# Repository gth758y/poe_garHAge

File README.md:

# poe_garHAge

in-work version of the PoE powered, MQTT garage door controller

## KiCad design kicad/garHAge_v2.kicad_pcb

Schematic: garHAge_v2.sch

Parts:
C1, C2: 6.8n; C_0805_2012Metric
C3: 22n; C_0805_2012Metric
C4: 10n; C_0805_2012Metric
C5, C6: 18p; C_0603_1608Metric
C7, C8, C9: 100n; C_0805_2012Metric
D1: BLUE; LED_1206_3216Metric_Pad1.42x1.75mm_HandSolder
D2: RED; LED_1206_3216Metric_Pad1.42x1.75mm_HandSolder
J1, J2, J3: SJ1-2503A; Headphone_Jack_2.5mm_SJ1-2503A; MPN SJ1-2503A; Digi-Key_PN CP1-2503A-ND
J4: 0813-1X1T-57-F; 0813-1X1T-57-F_RJ45-Jack; DigiKey Part Number 507-1421-ND
L1: 1uH; C_0805_2012Metric
R1, R2, R3, R4: 49.9; R_0805_2012Metric
R5, R7: 330; R_0805_2012Metric
R6: 12k; R_0805_2012Metric
U1: ATMEGA328P-AU; TQFP-32_7x7mm; MPN ATMEGA328P-AU; Digi-Key_PN ATMEGA328P-AU-ND
X1: ICSP; PinHeader_2x03_P2.54mm_Vertical
X2: Serial Pwr Disconnect; PinHeader_1x02_P2.54mm_Vertical
X3: Serial Interface; PinHeader_1x06_P2.54mm_Horizontal
Y1: 8MHz; Crystal_SMD_5032-2Pin_5.0x3.2mm

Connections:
+3V3: C8.1, C9.1, L1.1, R1.1, R2.1, R5.2, R6.2, U1.4 (VCC), U1.6 (VCC), U1.18 (AVCC), U1.20 (AREF), X1.2, X2.2; also elsewhere on the board
/BOOT_STATUS: D2.2 (A), R7.2
/CT: C3.2, J4.7 (CT), L1.2
/PoE_PD_Interface/VC12: J4.5 (VC12); also elsewhere on the board
/PoE_PD_Interface/VC36: J4.10 (VC36); also elsewhere on the board
/PoE_PD_Interface/VC45: J4.6 (VC45); also elsewhere on the board
/PoE_PD_Interface/VC78: J4.11 (VC78); also elsewhere on the board
/RD+: C2.2, J4.2 (RD+), R3.2
/RD-: C1.2, J4.9 (RD-), R4.2
/W5100_Ethernet_Interface/RD+: C2.1; also elsewhere on the board
/W5100_Ethernet_Interface/RD-: C1.1; also elsewhere on the board
/W5100_Ethernet_Interface/TD+: J4.1 (TD+), R1.2; also elsewhere on the board
/W5100_Ethernet_Interface/TD-: J4.8 (TD-), R2.2; also elsewhere on the board
D1RELAY: U1.9 (PD5); also elsewhere on the board
D1SENSOR: J1.1 (S), U1.10 (PD6)
D2RELAY: U1.2 (PD4); also elsewhere on the board
D2SENSOR: J2.1 (S), U1.11 (PD7)
D3RELAY: U1.1 (PD3); also elsewhere on the board
D3SENSOR: J3.1 (S), U1.12 (PB0)
DTR: C7.1, X3.6
GND: C3.1, C4.1, C5.1, C6.2, C8.2, C9.2, D1.1 (K), D2.1 (K), J1.4 (R), J2.4 (R), J3.4 (R), U1.3 (GND), U1.5 (GND), U1.21 (GND), X1.6, X3.1, X3.2; also elsewhere on the board
INT: U1.32 (PD2); also elsewhere on the board
MISO: U1.16 (PB4), X1.1; also elsewhere on the board
MOSI: U1.15 (PB3), X1.4; also elsewhere on the board
unnamed: C4.2, R3.1, R4.1
unnamed: C5.2, U1.7 (PB6), Y1.1
unnamed: C6.1, U1.8 (PB7), Y1.2
unnamed: D1.2 (A), R5.1
unnamed: R7.1, U1.25 (PC2)
unnamed: X2.1, X3.3
RESET: C7.2, R6.1, U1.29 (PC6), X1.5; also elsewhere on the board
RXI: U1.30 (PD0), X3.4
SCK: U1.17 (PB5), X1.3; also elsewhere on the board
SS: U1.14 (PB2); also elsewhere on the board
TXO: U1.31 (PD1), X3.5

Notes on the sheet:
ICSP Interface
Serial Debug Interface
Power Indication
Relay Interface
Reed Switch Interface
Ethernet and 802.3af PoE Interface
ATMEGA328P MCU

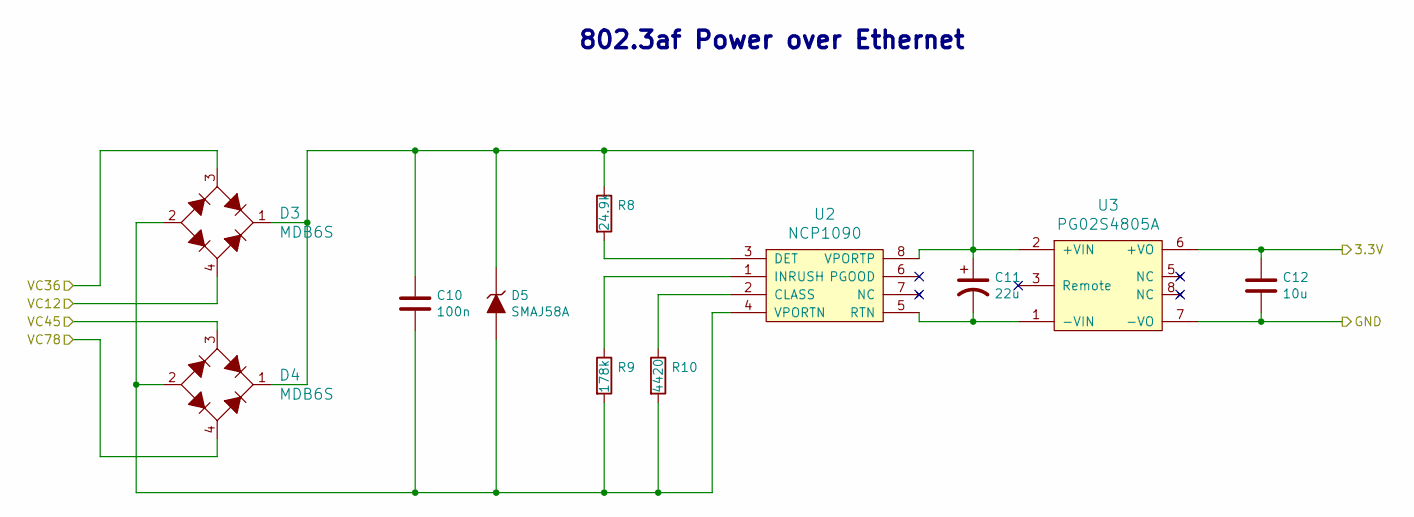
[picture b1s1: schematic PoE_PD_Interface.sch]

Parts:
C10: 100n; C_0805_2012Metric
C11: 22u; CP_Radial_D5.0mm_P2.00mm
C12: 10u; C_0805_2012Metric
D3, D4: MDB6S; Micro-DIP-4; DigiKey Part Number MDB6SFSCT-ND
D5: SMAJ58A; D_SMA
R8: 24.9k; R_0805_2012Metric
R9: 178k; R_0805_2012Metric
R10: 4420; R_0805_2012Metric
U2: NCP1090; SOIC-8_3.9x4.9mm_P1.27mm; DigiKey Part Number NCP1090DGOS-ND
U3: PG02S4805A; PG02S; DigiKey Part Number 941-1186-ND

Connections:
+3V3: C12.1, U3.6 (+VO); also elsewhere on the board
/PoE_PD_Interface/VC12: D3.4 (AC2); also elsewhere on the board
/PoE_PD_Interface/VC36: D3.3 (AC1); also elsewhere on the board
/PoE_PD_Interface/VC45: D4.3 (AC1); also elsewhere on the board
/PoE_PD_Interface/VC78: D4.4 (AC2); also elsewhere on the board
GND: C12.2, U3.7 (-VO); also elsewhere on the board
unnamed: C10.1, C11.1, D3.1 (+), D4.1 (+), D5.1 (K), R8.1, U2.8 (VPORTP), U3.2 (+VIN)
unnamed: C10.2, D3.2 (-), D4.2 (-), D5.2 (A), R9.2, R10.2, U2.4 (VPORTN)
unnamed: C11.2, U2.5 (RTN), U3.1 (-VIN)
unnamed: R8.2, U2.3 (DET)
unnamed: R9.1, U2.1 (INRUSH)
unnamed: R10.1, U2.2 (CLASS)

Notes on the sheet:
802.3af Power over Ethernet

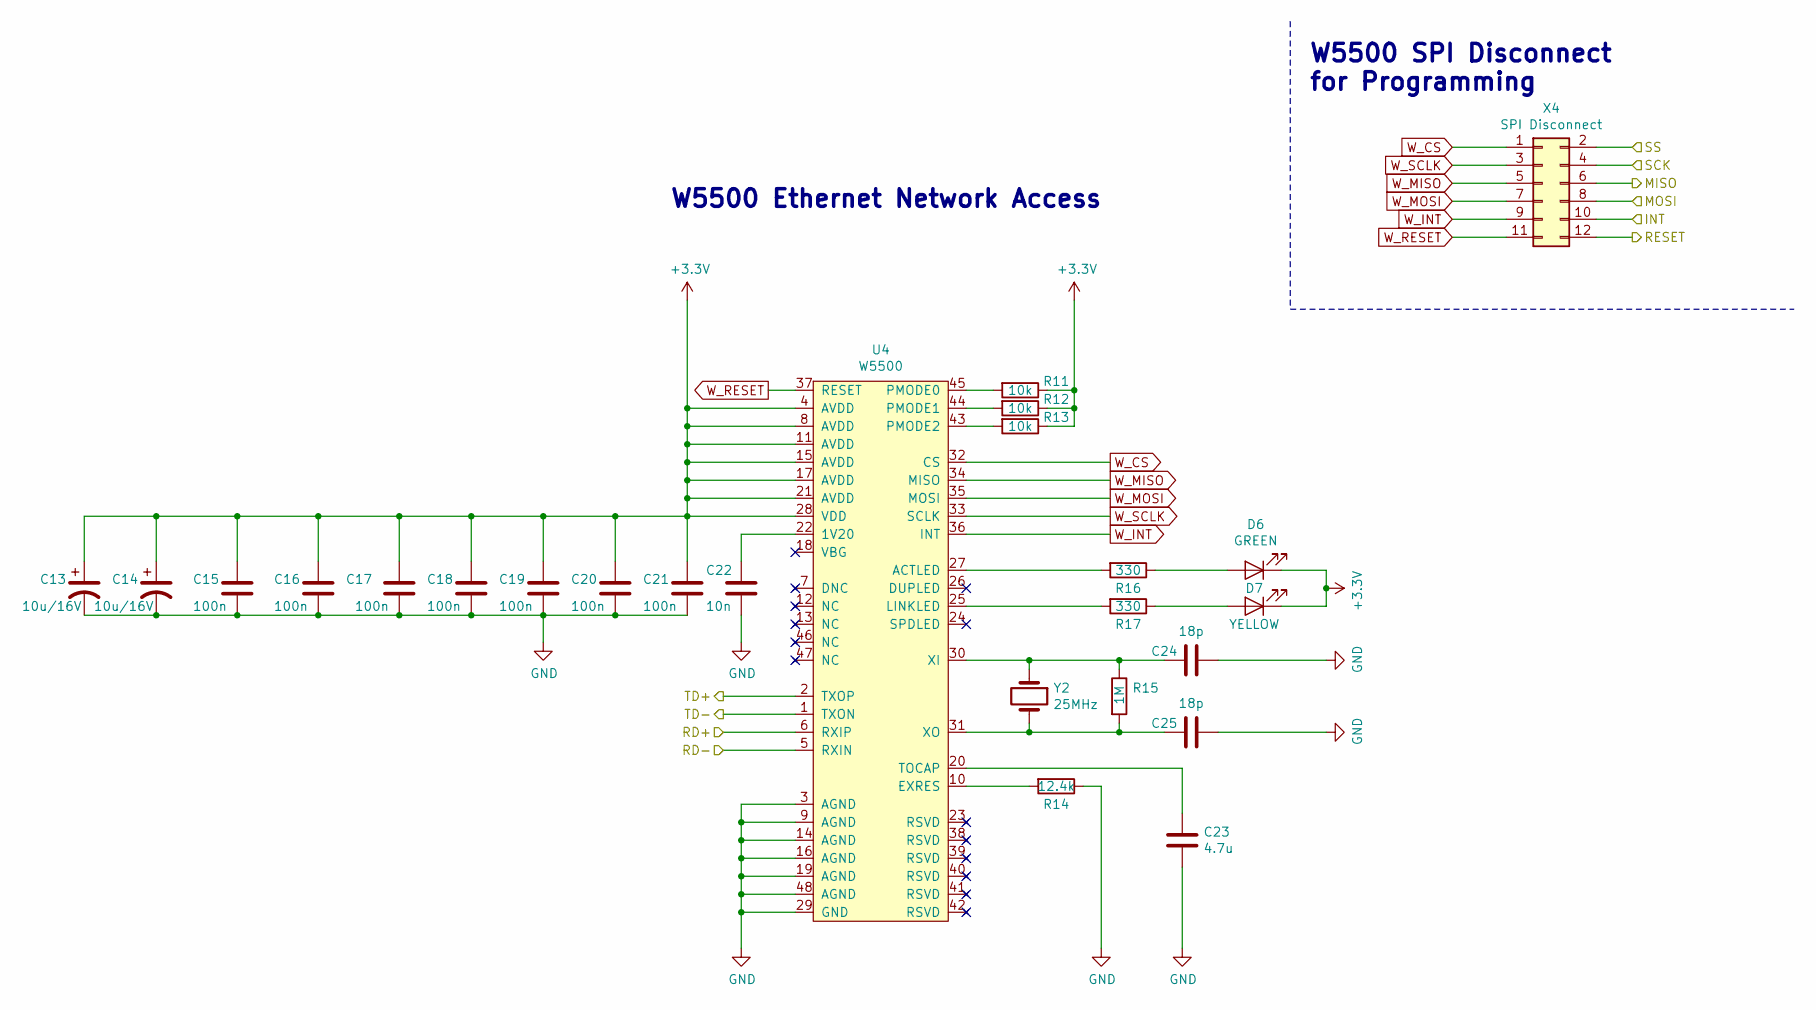
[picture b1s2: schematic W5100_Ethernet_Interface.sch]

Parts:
C13, C14: 10u/16V; C_0805_2012Metric
C15, C16, C17, C18, C19, C20, C21: 100n; C_0805_2012Metric
C22: 10n; C_0805_2012Metric
C23: 4.7u; C_0805_2012Metric
C24, C25: 18p; C_0603_1608Metric
D6: GREEN; LED_1206_3216Metric_Pad1.42x1.75mm_HandSolder
D7: YELLOW; LED_1206_3216Metric_Pad1.42x1.75mm_HandSolder
R11, R12, R13: 10k; R_0805_2012Metric
R14: 12.4k; R_0805_2012Metric
R15: 1M; R_0805_2012Metric
R16, R17: 330; R_0805_2012Metric
U4: W5500; LQFP-48_7x7mm_P0.5mm
X4: SPI Disconnect; PinHeader_2x06_P2.54mm_Vertical
Y2: 25MHz; Crystal_SMD_5032-2Pin_5.0x3.2mm

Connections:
+3V3: C13.1, C14.1, C15.1, C16.1, C17.1, C18.1, C19.1, C20.1, C21.1, D6.1 (K), D7.1 (K), R11.1, R12.1, R13.1, U4.4 (AVDD), U4.8 (AVDD), U4.11 (AVDD), U4.15 (AVDD), U4.17 (AVDD), U4.21 (AVDD), U4.28 (VDD); also elsewhere on the board
/W5100_Ethernet_Interface/RD+: U4.6 (RXIP); also elsewhere on the board
/W5100_Ethernet_Interface/RD-: U4.5 (RXIN); also elsewhere on the board
/W5100_Ethernet_Interface/TD+: U4.2 (TXOP); also elsewhere on the board
/W5100_Ethernet_Interface/TD-: U4.1 (TXON); also elsewhere on the board
GND: C13.2, C14.2, C15.2, C16.2, C17.2, C18.2, C19.2, C20.2, C21.2, C22.2, C23.2, C24.1, C25.1, R14.1, U4.3 (AGND), U4.9 (AGND), U4.14 (AGND), U4.16 (AGND), U4.19 (AGND), U4.29 (GND), U4.48 (AGND); also elsewhere on the board
INT: X4.10; also elsewhere on the board
MISO: X4.6; also elsewhere on the board
MOSI: X4.8; also elsewhere on the board
unnamed: C22.1, U4.22 (1V20)
unnamed: C23.1, U4.20 (TOCAP)
unnamed: C24.2, R15.1, U4.30 (XI), Y2.1
unnamed: C25.2, R15.2, U4.31 (XO), Y2.2
unnamed: D6.2 (A), R16.1
unnamed: D7.2 (A), R17.1
unnamed: R11.2, U4.45 (PMODE0)
unnamed: R12.2, U4.44 (PMODE1)
unnamed: R13.2, U4.43 (PMODE2)
unnamed: R14.2, U4.10 (EXRES)
unnamed: R16.2, U4.27 (ACTLED)
unnamed: R17.2, U4.25 (LINKLED)
RESET: X4.12; also elsewhere on the board
SCK: X4.4; also elsewhere on the board
SS: X4.2; also elsewhere on the board
W_CS: U4.32 (CS), X4.1
W_INT: U4.36 (INT), X4.9
W_MISO: U4.34 (MISO), X4.5
W_MOSI: U4.35 (MOSI), X4.7
W_RESET: U4.37 (RESET), X4.11
W_SCLK: U4.33 (SCLK), X4.3

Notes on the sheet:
W5500 SPI Disconnect for Programming
W5500 Ethernet Network Access

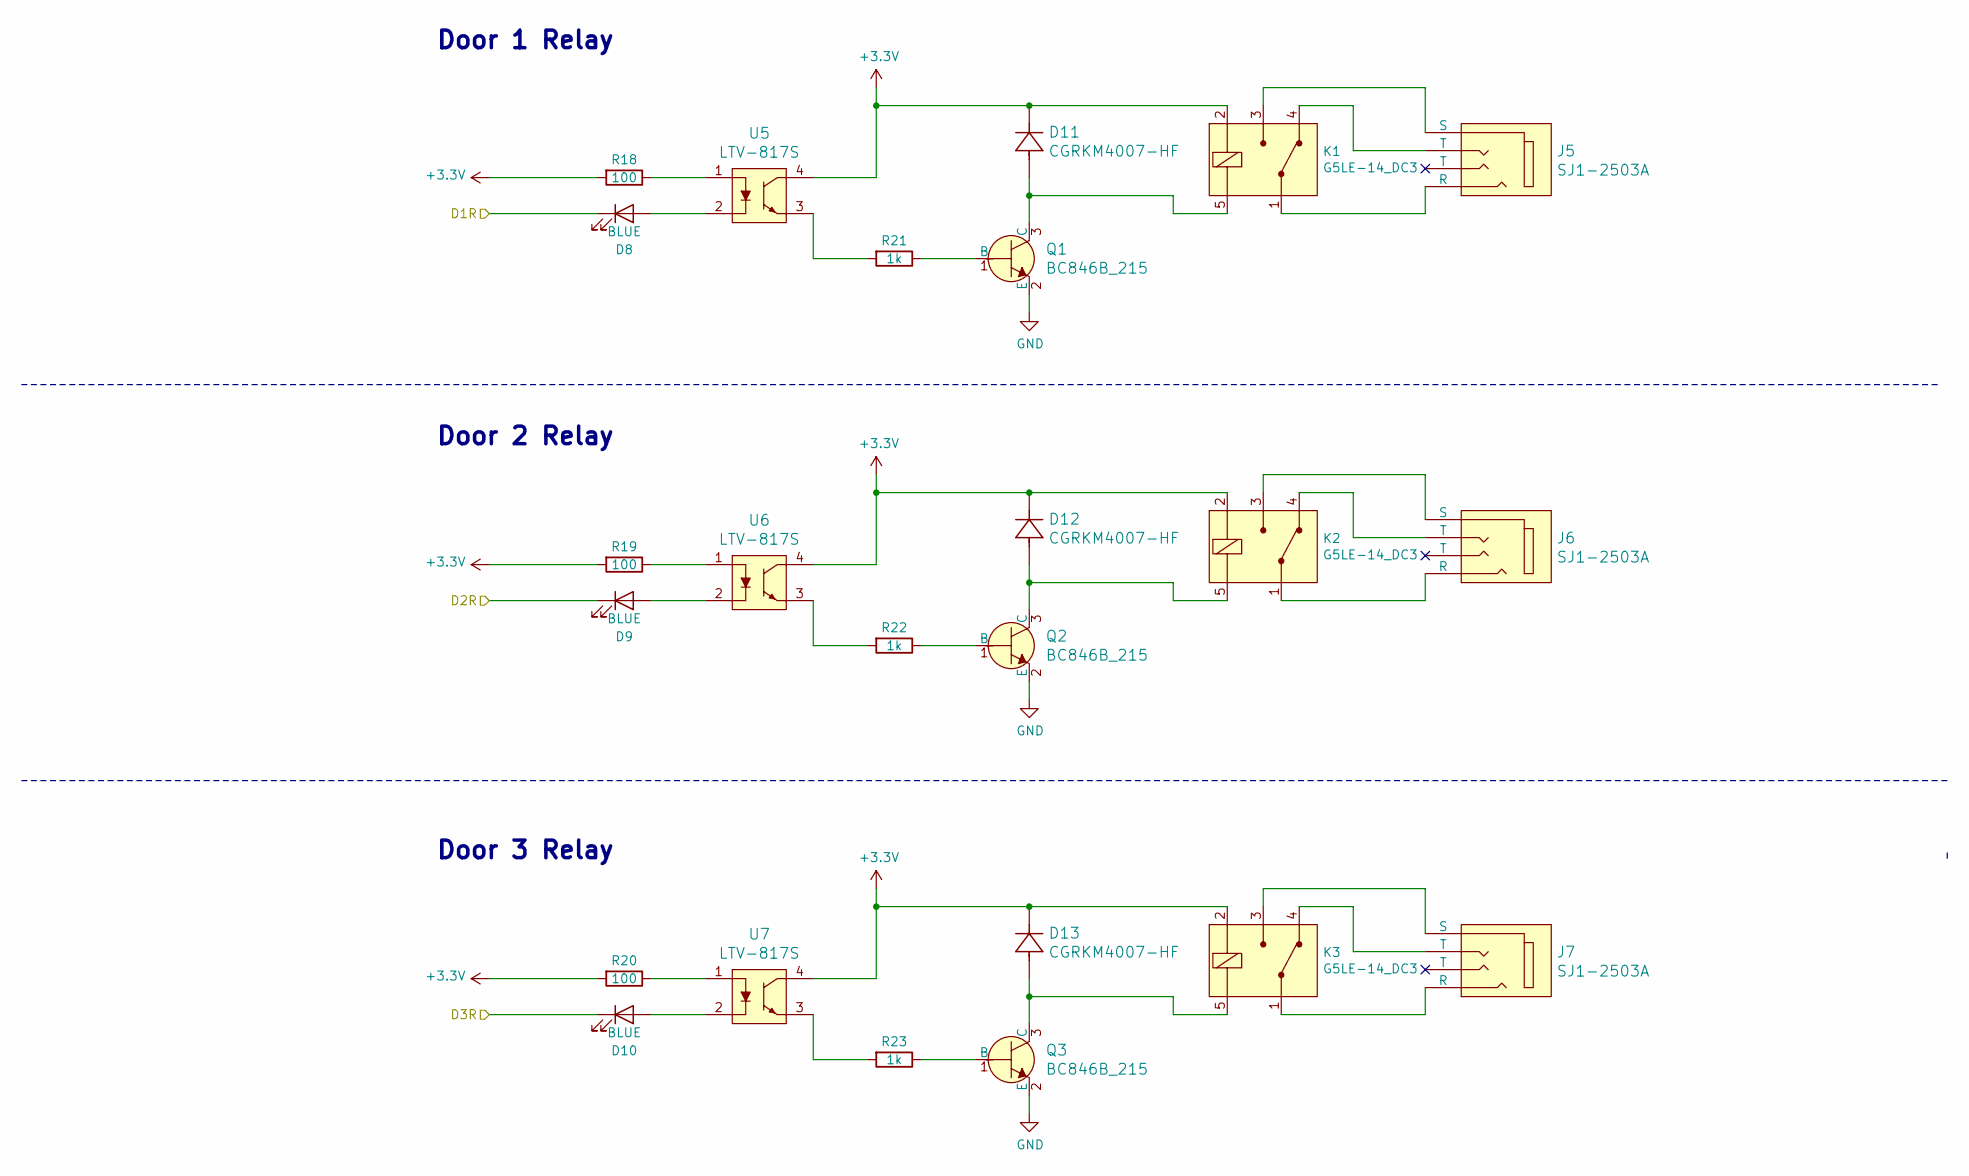
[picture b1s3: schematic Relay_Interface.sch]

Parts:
D8, D9, D10: BLUE; LED_1206_3216Metric_Pad1.42x1.75mm_HandSolder
D11, D12, D13: CGRKM4007-HF; D_SOD-123F
J5, J6, J7: SJ1-2503A; Headphone_Jack_2.5mm_SJ1-2503A; MPN SJ1-2503A; Digi-Key_PN CP1-2503A-ND
K1, K2, K3: G5LE-14_DC3; Relay_THT_G5LE-14; MPN G5LE-14 DC3; Digi-Key_PN Z3326-ND
Q1, Q2, Q3: BC846B_215; SOT-23-3; MPN BC846B,215; Digi-Key_PN 1727-2920-1-ND
R18, R19, R20: 100; R_0805_2012Metric
R21, R22, R23: 1k; R_0805_2012Metric
U5: LTV-817S; DIP-4_SMD_GullWing; MPN LTV-817; Digi-Key_PN 160-1366-5-ND
U6, U7: LTV-817S; DIP-4_SMD_GullWing; MPN LTV-817S; Digi-Key_PN 160-1366-5-ND

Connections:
+3V3: D11.1, D12.1, D13.1, K1.2 (COIL), K2.2 (COIL), K3.2 (COIL), R18.2, R19.2, R20.2, U5.4, U6.4, U7.4; also elsewhere on the board
D1RELAY: D8.1 (K); also elsewhere on the board
D2RELAY: D9.1 (K); also elsewhere on the board
D3RELAY: D10.1 (K); also elsewhere on the board
GND: Q1.2 (E), Q2.2 (E), Q3.2 (E); also elsewhere on the board
unnamed: D8.2 (A), U5.2
unnamed: D9.2 (A), U6.2
unnamed: D10.2 (A), U7.2
unnamed: D11.2, K1.5 (COIL), Q1.3 (C)
unnamed: D12.2, K2.5 (COIL), Q2.3 (C)
unnamed: D13.2, K3.5 (COIL), Q3.3 (C)
unnamed: J5.1 (S), K1.3 (NO)
unnamed: J5.3 (T), K1.4 (NC)
unnamed: J5.4 (R), K1.1 (COM)
unnamed: J6.1 (S), K2.3 (NO)
unnamed: J6.3 (T), K2.4 (NC)
unnamed: J6.4 (R), K2.1 (COM)
unnamed: J7.1 (S), K3.3 (NO)
unnamed: J7.3 (T), K3.4 (NC)
unnamed: J7.4 (R), K3.1 (COM)
unnamed: Q1.1 (B), R21.1
unnamed: Q2.1 (B), R22.1
unnamed: Q3.1 (B), R23.1
unnamed: R18.1, U5.1
unnamed: R19.1, U6.1
unnamed: R20.1, U7.1
unnamed: R21.2, U5.3
unnamed: R22.2, U6.3
unnamed: R23.2, U7.3

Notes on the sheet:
Door 1 Relay
Door 2 Relay
Door 3 Relay

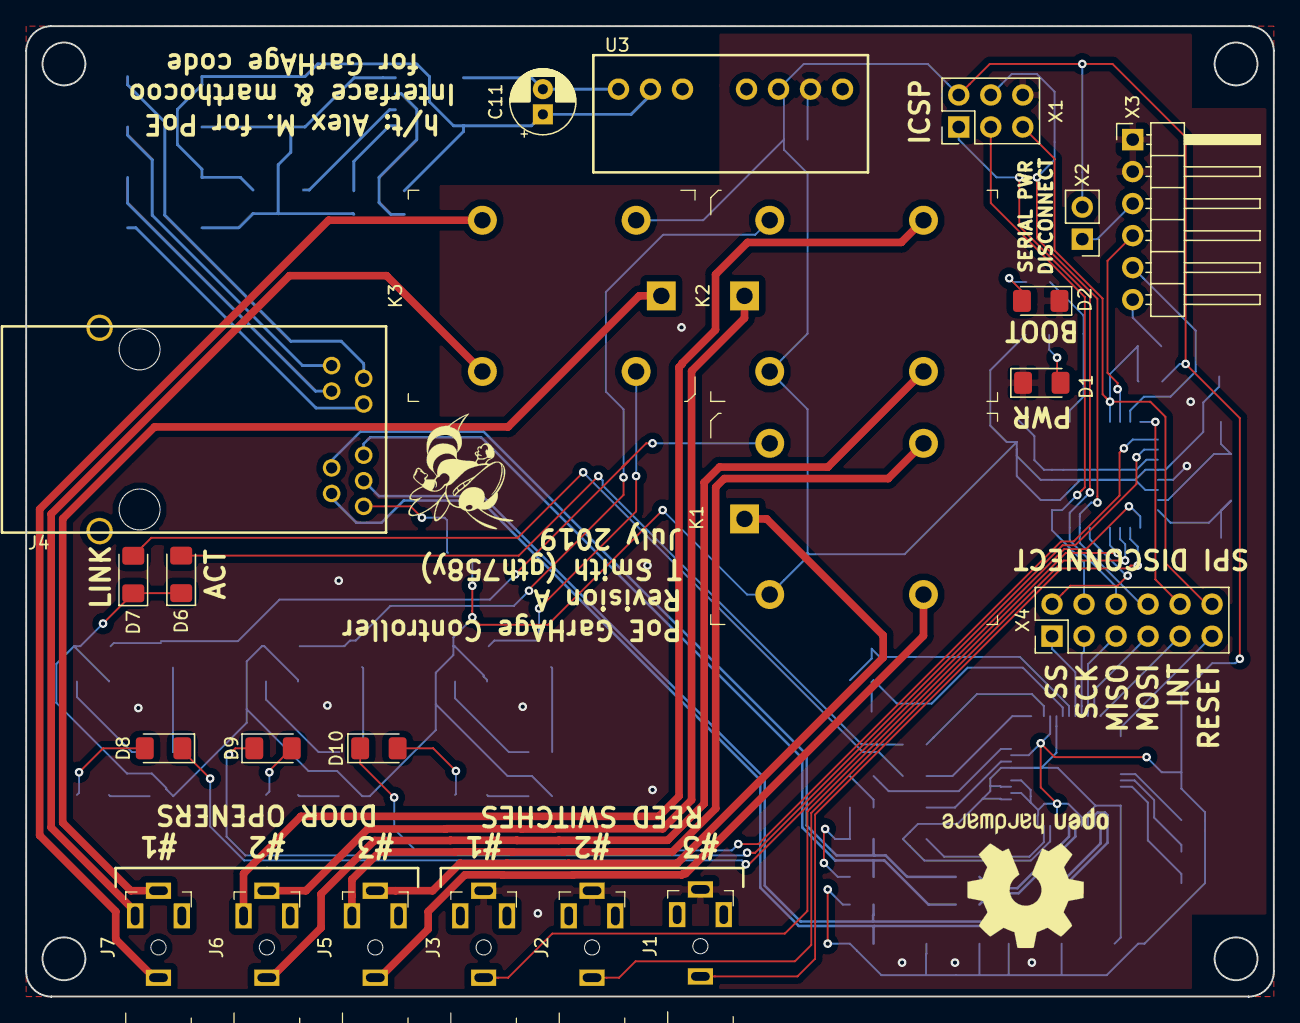
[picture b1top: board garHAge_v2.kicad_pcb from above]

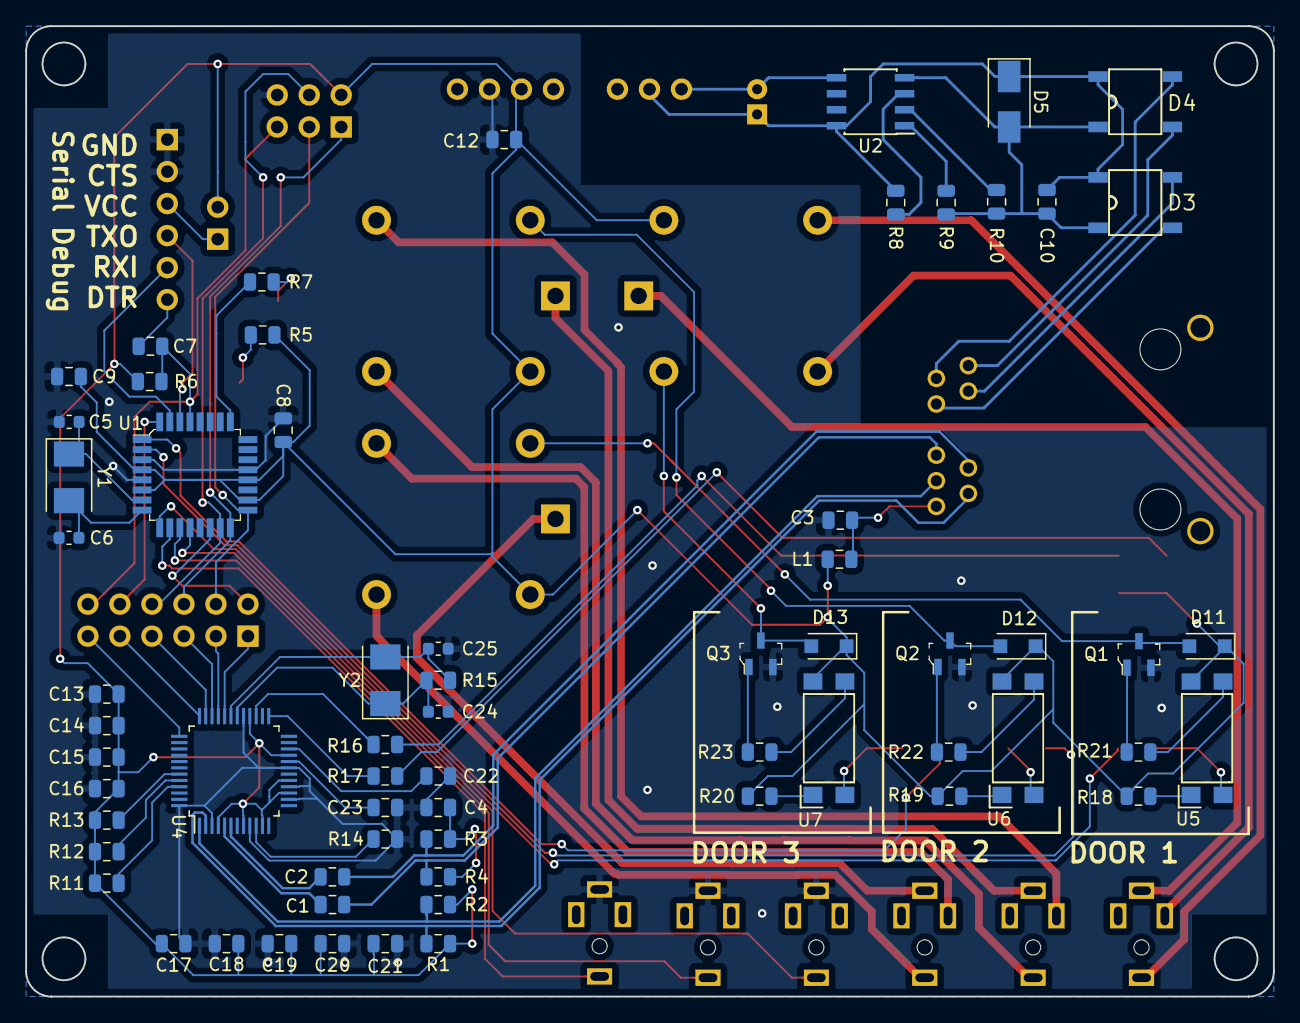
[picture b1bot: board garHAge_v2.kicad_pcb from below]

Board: 2 copper layers, 99.0 x 77.0 mm, 88 parts (65 on the bottom side), 83 nets.

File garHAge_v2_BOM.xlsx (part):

Source: | Z:\00 - tyler\arduino projects\poe garHAge\garHAge_v2\garHAge_v2.sch
Date: | 43660.793032407404
Tool: | Eeschema (5.0.2)-1
Generator: | C:\Program Files\KiCad\bin\scripting\plugins/bom_csv_grouped_by_value.py
Component Count: | 88
Individual Components:
Item | Qty | Reference(s) | Value | LibPart | Footprint | Digi-Key_PN | DigiKey Part Number | Description | Datasheet | Category | DK_Datasheet_Link | DK_Detail_Page | Family | MPN | Manufacturer | Status
 |  | C1 | 6.8n | Device:C | Capacitor_SMD:C_0805_2012Metric |  |  |  | ~
 |  | C2 | 6.8n | Device:C | Capacitor_SMD:C_0805_2012Metric |  |  |  | ~
 |  | C3 | 22n | Device:C | Capacitor_SMD:C_0805_2012Metric |  |  |  | ~
 |  | C4 | 10n | Device:C | Capacitor_SMD:C_0805_2012Metric |  |  |  | ~
 |  | C5 | 18p | Device:C | Capacitor_SMD:C_0603_1608Metric |  |  |  | ~
 |  | C6 | 18p | Device:C | Capacitor_SMD:C_0603_1608Metric |  |  |  | ~
 |  | C7 | 100n | Device:C | Capacitor_SMD:C_0805_2012Metric |  |  |  | ~
 |  | C8 | 100n | Device:C | Capacitor_SMD:C_0805_2012Metric |  |  |  | ~
 |  | C9 | 100n | Device:C | Capacitor_SMD:C_0805_2012Metric |  |  |  | ~
 |  | C10 | 100n | Device:C | Capacitor_SMD:C_0805_2012Metric |  |  |  | ~
 |  | C11 | 22u | Device:CP1 | Capacitor_THT:CP_Radial_D5.0mm_P2.00mm |  |  |  | ~
 |  | C12 | 10u | Device:C | Capacitor_SMD:C_0805_2012Metric |  |  |  | ~
 |  | C13 | 10u/16V | Device:CP1 | Capacitor_SMD:C_0805_2012Metric |  |  |  | ~
 |  | C14 | 10u/16V | Device:CP1 | Capacitor_SMD:C_0805_2012Metric |  |  |  | ~
 |  | C15 | 100n | Device:C | Capacitor_SMD:C_0805_2012Metric |  |  |  | ~
 |  | C16 | 100n | Device:C | Capacitor_SMD:C_0805_2012Metric |  |  |  | ~
 |  | C17 | 100n | Device:C | Capacitor_SMD:C_0805_2012Metric |  |  |  | ~
 |  | C18 | 100n | Device:C | Capacitor_SMD:C_0805_2012Metric |  |  |  | ~
 |  | C19 | 100n | Device:C | Capacitor_SMD:C_0805_2012Metric |  |  |  | ~
 |  | C20 | 100n | Device:C | Capacitor_SMD:C_0805_2012Metric |  |  |  | ~
 |  | C21 | 100n | Device:C | Capacitor_SMD:C_0805_2012Metric |  |  |  | ~
 |  | C22 | 10n | Device:C | Capacitor_SMD:C_0805_2012Metric |  |  |  | ~
 |  | C23 | 4.7u | Device:C | Capacitor_SMD:C_0805_2012Metric |  |  |  | ~
 |  | C24 | 18p | Device:C | Capacitor_SMD:C_0603_1608Metric |  |  |  | ~
 |  | C25 | 18p | Device:C | Capacitor_SMD:C_0603_1608Metric |  |  |  | ~
 |  | D1 | LED | Device:LED | LED_SMD:LED_1206_3216Metric_Pad1.42x1.75mm_HandSolder |  |  |  | ~
 |  | D2 | LED | Device:LED | LED_SMD:LED_1206_3216Metric_Pad1.42x1.75mm_HandSolder |  |  |  | ~
 |  | D3 | MDB6S | LoadCell-cache:MDB6S | tyler_components:Micro-DIP-4 |  | MDB6SFSCT-ND |  | https://www.fairchildsemi.com/datasheets/MD/MDB10S.pdf
 |  | D4 | MDB6S | LoadCell-cache:MDB6S | tyler_components:Micro-DIP-4 |  | MDB6SFSCT-ND |  | https://www.fairchildsemi.com/datasheets/MD/MDB10S.pdf
 |  | D5 | SMAJ58A | LoadCell-cache:ZENER | Diode_SMD:D_SMA
 |  | D6 | LED | Device:LED | LED_SMD:LED_1206_3216Metric_Pad1.42x1.75mm_HandSolder |  |  |  | ~
 |  | D7 | LED | Device:LED | LED_SMD:LED_1206_3216Metric_Pad1.42x1.75mm_HandSolder |  |  |  | ~
 |  | D8 | LED | Device:LED | LED_SMD:LED_1206_3216Metric_Pad1.42x1.75mm_HandSolder |  |  |  | ~
 |  | D9 | LED | Device:LED | LED_SMD:LED_1206_3216Metric_Pad1.42x1.75mm_HandSolder |  |  |  | ~
 |  | D10 | LED | Device:LED | LED_SMD:LED_1206_3216Metric_Pad1.42x1.75mm_HandSolder |  |  |  | ~
 |  | D11 | CGRKM4007-HF | dk_CGRKM4007-HF:CGRKM4007-HF | Diode_SMD:D_SOD-123F
 |  | D12 | CGRKM4007-HF | dk_CGRKM4007-HF:CGRKM4007-HF | Diode_SMD:D_SOD-123F
 |  | D13 | CGRKM4007-HF | dk_CGRKM4007-HF:CGRKM4007-HF | Diode_SMD:D_SOD-123F
 |  | J1 | SJ1-2503A | dk_Barrel-Audio-Connectors:SJ1-2503A | digikey-footprints:Headphone_Jack_2.5mm_SJ1-2503A | CP1-2503A-ND |  | CONN JACK STEREO 2.5MM R/A | https://www.cui.com/product/resource/digikeypdf/sj1-2503a.pdf | Connectors, Interconnects | https://www.cui.com/product/resource/digikeypdf/sj1-2503a.pdf | /product-detail/en/cui-inc/SJ1-2503A/CP1-2503A-ND/738680 | Barrel - Audio Connectors | SJ1-2503A | CUI Inc. | Active
 |  | J2 | SJ1-2503A | dk_Barrel-Audio-Connectors:SJ1-2503A | digikey-footprints:Headphone_Jack_2.5mm_SJ1-2503A | CP1-2503A-ND |  | CONN JACK STEREO 2.5MM R/A | https://www.cui.com/product/resource/digikeypdf/sj1-2503a.pdf | Connectors, Interconnects | https://www.cui.com/product/resource/digikeypdf/sj1-2503a.pdf | /product-detail/en/cui-inc/SJ1-2503A/CP1-2503A-ND/738680 | Barrel - Audio Connectors | SJ1-2503A | CUI Inc. | Active
 |  | J3 | SJ1-2503A | dk_Barrel-Audio-Connectors:SJ1-2503A | digikey-footprints:Headphone_Jack_2.5mm_SJ1-2503A | CP1-2503A-ND |  | CONN JACK STEREO 2.5MM R/A | https://www.cui.com/product/resource/digikeypdf/sj1-2503a.pdf | Connectors, Interconnects | https://www.cui.com/product/resource/digikeypdf/sj1-2503a.pdf | /product-detail/en/cui-inc/SJ1-2503A/CP1-2503A-ND/738680 | Barrel - Audio Connectors | SJ1-2503A | CUI Inc. | Active
 |  | J4 | 0813-1X1T-57-F | LoadCell-rescue:0813-1X1T-57-F | tyler_components:0813-1X1T-57-F_RJ45-Jack |  | 507-1421-ND |  | http://belfuse.com/pdfs/0813-1X1T-57-F.pdf
 |  | J5 | SJ1-2503A | dk_Barrel-Audio-Connectors:SJ1-2503A | digikey-footprints:Headphone_Jack_2.5mm_SJ1-2503A | CP1-2503A-ND |  | CONN JACK STEREO 2.5MM R/A | https://www.cui.com/product/resource/digikeypdf/sj1-2503a.pdf | Connectors, Interconnects | https://www.cui.com/product/resource/digikeypdf/sj1-2503a.pdf | /product-detail/en/cui-inc/SJ1-2503A/CP1-2503A-ND/738680 | Barrel - Audio Connectors | SJ1-2503A | CUI Inc. | Active
 |  | J6 | SJ1-2503A | dk_Barrel-Audio-Connectors:SJ1-2503A | digikey-footprints:Headphone_Jack_2.5mm_SJ1-2503A | CP1-2503A-ND |  | CONN JACK STEREO 2.5MM R/A | https://www.cui.com/product/resource/digikeypdf/sj1-2503a.pdf | Connectors, Interconnects | https://www.cui.com/product/resource/digikeypdf/sj1-2503a.pdf | /product-detail/en/cui-inc/SJ1-2503A/CP1-2503A-ND/738680 | Barrel - Audio Connectors | SJ1-2503A | CUI Inc. | Active
 |  | J7 | SJ1-2503A | dk_Barrel-Audio-Connectors:SJ1-2503A | digikey-footprints:Headphone_Jack_2.5mm_SJ1-2503A | CP1-2503A-ND |  | CONN JACK STEREO 2.5MM R/A | https://www.cui.com/product/resource/digikeypdf/sj1-2503a.pdf | Connectors, Interconnects | https://www.cui.com/product/resource/digikeypdf/sj1-2503a.pdf | /product-detail/en/cui-inc/SJ1-2503A/CP1-2503A-ND/738680 | Barrel - Audio Connectors | SJ1-2503A | CUI Inc. | Active
 |  | K1 | G5LE-14_DC3 | dk_Power-Relays-Over-2-Amps:G5LE-14_DC5 | digikey-footprints:Relay_THT_G5LE-14 | Z3326-ND |  | RELAY GEN PURPOSE SPDT 10A 5V | https://omronfs.omron.com/en_US/ecb/products/pdf/en-g5le.pdf | Relays | https://omronfs.omron.com/en_US/ecb/products/pdf/en-g5le.pdf | /product-detail/en/omron-electronics-inc-emc-div/G5LE-14-DC3/Z3326-ND/1815628 | Power Relays, Over 2 Amps | G5LE-14 DC3 | Omron Electronics Inc-EMC Div | Active
 |  | K2 | G5LE-14_DC3 | dk_Power-Relays-Over-2-Amps:G5LE-14_DC5 | digikey-footprints:Relay_THT_G5LE-14 | Z3326-ND |  | RELAY GEN PURPOSE SPDT 10A 5V | https://omronfs.omron.com/en_US/ecb/products/pdf/en-g5le.pdf | Relays | https://omronfs.omron.com/en_US/ecb/products/pdf/en-g5le.pdf | /product-detail/en/omron-electronics-inc-emc-div/G5LE-14-DC3/Z3326-ND/1815628 | Power Relays, Over 2 Amps | G5LE-14 DC3 | Omron Electronics Inc-EMC Div | Active
 |  | K3 | G5LE-14_DC3 | dk_Power-Relays-Over-2-Amps:G5LE-14_DC5 | digikey-footprints:Relay_THT_G5LE-14 | Z3326-ND |  | RELAY GEN PURPOSE SPDT 10A 5V | https://omronfs.omron.com/en_US/ecb/products/pdf/en-g5le.pdf | Relays | https://omronfs.omron.com/en_US/ecb/products/pdf/en-g5le.pdf | /product-detail/en/omron-electronics-inc-emc-div/G5LE-14-DC3/Z3326-ND/1815628 | Power Relays, Over 2 Amps | G5LE-14 DC3 | Omron Electronics Inc-EMC Div | Active
 |  | L1 | 1uH | Device:L | Capacitor_SMD:C_0805_2012Metric |  |  |  | ~
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
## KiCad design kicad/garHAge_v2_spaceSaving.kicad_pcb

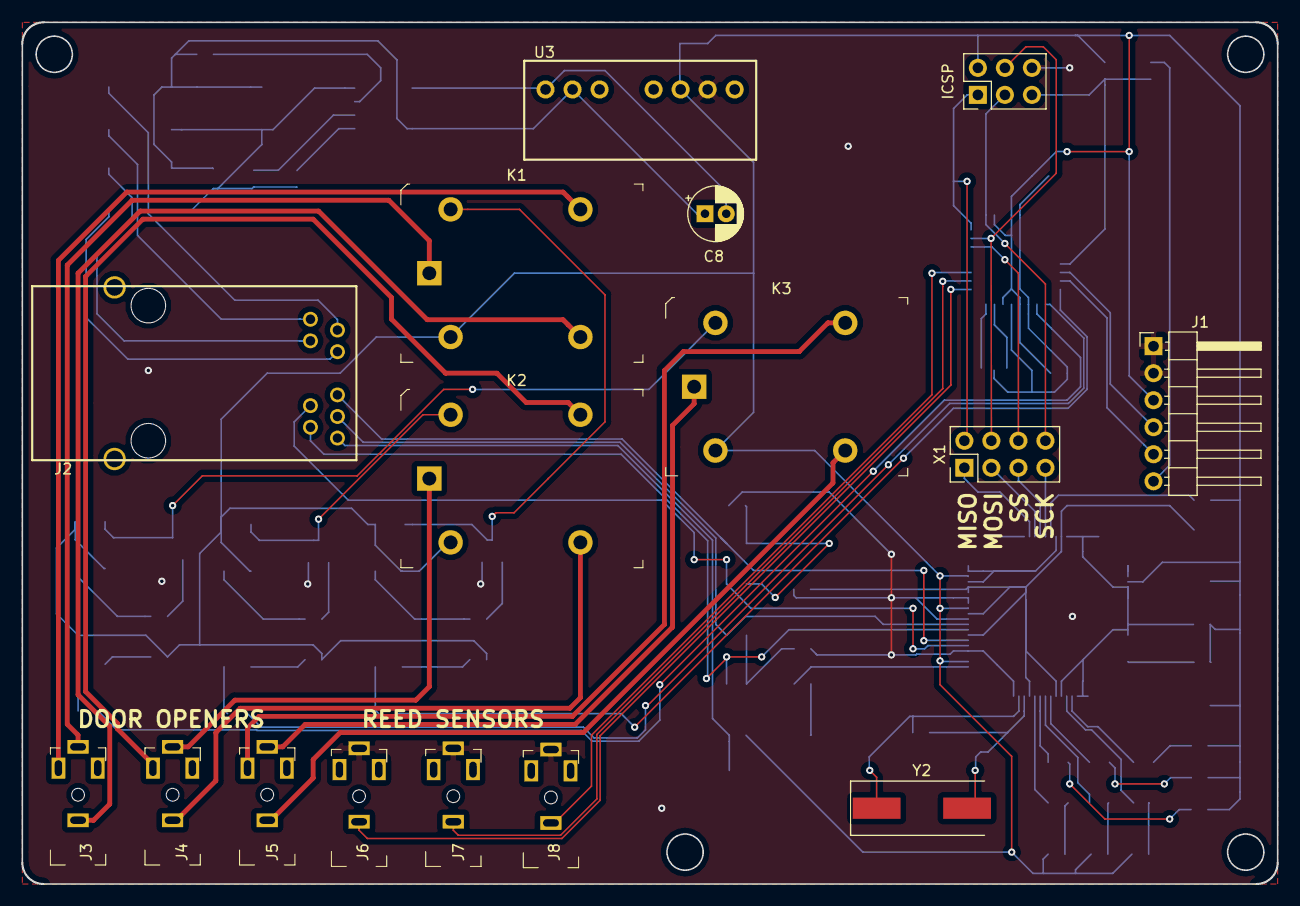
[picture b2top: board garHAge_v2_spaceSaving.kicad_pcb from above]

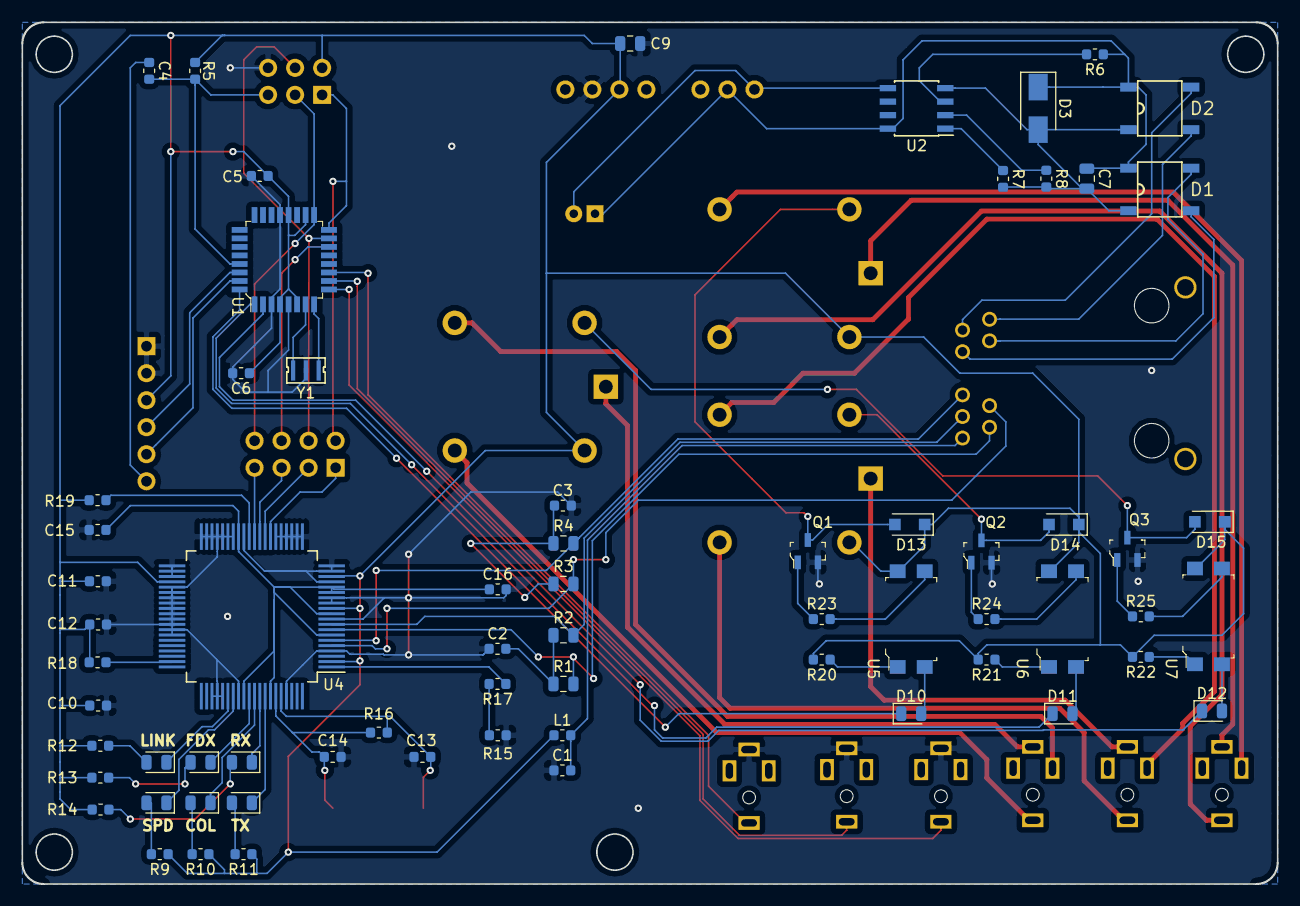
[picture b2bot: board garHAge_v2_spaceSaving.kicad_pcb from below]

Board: 2 copper layers, 118.0 x 81.0 mm, 82 parts (66 on the bottom side), 82 nets.

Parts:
C1, C2, C3, C4, C5, C6, C10, C11, C12, C15, C16: 100n; C_0603_1608Metric
C7: 100n; C_0805_2012Metric
C8: 22u; CP_Radial_D5.0mm_P2.00mm
C9: 10u; C_0805_2012Metric
C13, C14: 18p; C_0603_1608Metric
D1, D2: MDB6S; Micro-DIP-4
D3: SMAJ58A; D_SMA
D4, D5, D6, D7, D8, D9, D10, D11, D12: LED; LED_0805_2012Metric
D13, D14, D15: CGRKM4007-HF; D_SOD-123F
ICSP: ICSP; PinHeader_2x03_P2.54mm_Vertical
J1: Serial Interface; PinHeader_1x06_P2.54mm_Horizontal
J2: 0813-1X1T-57-F; 0813-1X1T-57-F_RJ45-Jack
J3, J4, J5, J6, J7, J8: SJ1-2503A; Headphone_Jack_2.5mm_SJ1-2503A
K1, K2, K3: G5LE-14_DC3; Relay_THT_G5LE-14
L1: 1uH; C_0603_1608Metric
Q1, Q2, Q3: BC846B_215; SOT-23-3
R1, R2, R3, R4: 49.9; R_0805_2012Metric
R5, R17, R18, R19: 12k; R_0603_1608Metric
R6: 24.9k; R_0603_1608Metric
R7: 178k; R_0603_1608Metric
R8: 4420; R_0603_1608Metric
R9, R10, R11, R12, R13, R14: 470; R_0603_1608Metric
R15: 300; R_0603_1608Metric
R16: 1M; R_0603_1608Metric
R20, R21, R22: 1k; R_0603_1608Metric
R23, R24, R25: 510; R_0603_1608Metric
U1: ATMEGA328P-AU; TQFP-32_7x7mm
U2: NCP1090; SOIC-8_3.9x4.9mm_P1.27mm
U3: PG02S4805A; PG02S
U4: W5100; QFP-80_12x12_Pitch0.5mm_2.5mmpads
U5, U6, U7: LTV-817; SMD-4_4.6x7.62mm_P2.54mm
X1: SPI Disconnect; PinHeader_2x04_P2.54mm_Vertical
Y1: 8MHz; TylerComponent-3SMD-NonStandard-Resonator
Y2: 25MHz; Crystal_SMD_HC49-SD

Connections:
+3V3: C5.1, C6.1, C9.1, C10.1, C11.1, C12.1, D13.1, D14.1, D15.1, ICSP.2, J1.3, K1.2, K2.2, K3.2, L1.1, R5.2, R9.1, R10.1, R11.1, R12.1, R13.1, R14.1, R18.2, R19.1, R20.2, R21.2, R22.2, U1.4, U1.6, U1.18, U1.20, U3.6, U4.2, U4.12, U4.18, U4.44, U5.4, U6.4, U7.4
/PoE_PD_Interface/VC12: D1.4, J2.5
/PoE_PD_Interface/VC36: D1.3, J2.10
/PoE_PD_Interface/VC45: D2.3, J2.6
/PoE_PD_Interface/VC78: D2.4, J2.11
/W5100_Ethernet_Interface/RD+: J2.2, R3.2, U4.5
/W5100_Ethernet_Interface/RD-: J2.9, R4.2, U4.6
/W5100_Ethernet_Interface/TD+: J2.1, R1.2, U4.8
/W5100_Ethernet_Interface/TD-: J2.8, R2.2, U4.9
D1RELAY: D10.1, U1.32
D2RELAY: D11.1, U1.1
D3RELAY: D12.1, U1.2
DTR: C4.1, J1.6
GND: C1.1, C2.1, C3.1, C5.2, C6.2, C9.2, C10.2, C11.2, C12.2, C13.2, C14.2, C15.2, C16.2, ICSP.6, J1.1, J1.2, J6.4, J7.4, J8.4, Q1.2, Q2.2, Q3.2, R15.2, U1.3, U1.5, U1.21, U3.7, U4.4, U4.10, U4.13, U4.14, U4.17, U4.19, U4.20, U4.21, U4.22, U4.23, U4.24, U4.25, U4.26, U4.32, U4.34, U4.35, U4.36, U4.37, U4.38, U4.39, U4.40, U4.41, U4.42, U4.43, U4.45, U4.46, U4.47, U4.48, U4.49, U4.50, U4.51, U4.52, U4.53, U4.54, U4.63, U4.64, U4.65, U4.68, U4.77, Y1.2
MISO: ICSP.1, U1.16, X1.2
MOSI: ICSP.4, U1.15, X1.4
unnamed: C1.2, J2.7, L1.2
unnamed: C2.2, R1.1, R2.1
unnamed: C3.2, R3.1, R4.1
unnamed: C7.1, C8.1, D1.1, D2.1, D3.1, R6.1, U2.8, U3.2
unnamed: C7.2, D1.2, D2.2, D3.2, R7.2, R8.2, U2.4
unnamed: C8.2, U2.5, U3.1
unnamed: C13.1, R16.1, U4.76, Y2.1
unnamed: C14.1, R16.2, U4.75, Y2.2
unnamed: C15.1, C16.1, U4.7, U4.11, U4.15, U4.16, U4.33, U4.69, U4.74
unnamed: D4.1, U4.67
unnamed: D4.2, R9.2
unnamed: D5.1, U4.71
unnamed: D5.2, R10.2
unnamed: D6.1, U4.73
unnamed: D6.2, R11.2
unnamed: D7.1, U4.66
unnamed: D7.2, R12.2
unnamed: D8.1, U4.70
unnamed: D8.2, R13.2
unnamed: D9.1, U4.72
unnamed: D9.2, R14.2
unnamed: D10.2, U5.2
unnamed: D11.2, U6.2
unnamed: D12.2, U7.2
unnamed: D13.2, K1.5, Q1.3
unnamed: D14.2, K2.5, Q2.3
unnamed: D15.2, K3.5, Q3.3
unnamed: J3.1, K1.3
unnamed: J3.3, K1.4
unnamed: J3.4, K1.1
unnamed: J4.1, K2.3
unnamed: J4.3, K2.4
unnamed: J4.4, K2.1
unnamed: J5.1, K3.3
unnamed: J5.3, K3.4
unnamed: J5.4, K3.1
unnamed: J6.1, U1.9
unnamed: J7.1, U1.10
unnamed: J8.1, U1.11
unnamed: Q1.1, R23.1
unnamed: Q2.1, R24.1
unnamed: Q3.1, R25.1
unnamed: R6.2, U2.3
unnamed: R7.1, U2.1
unnamed: R8.1, U2.2
unnamed: R15.1, R17.2
unnamed: R17.1, U4.1
unnamed: R18.1, U4.59
unnamed: R19.2, U4.31
unnamed: R20.1, U5.1
unnamed: R21.1, U6.1
unnamed: R22.1, U7.1
unnamed: R23.2, U5.3
unnamed: R24.2, U6.3
unnamed: R25.2, U7.3
unnamed: U1.7, Y1.1
unnamed: U1.8, Y1.3
unnamed: U4.27, X1.1
unnamed: U4.28, X1.3
unnamed: U4.29, X1.5
unnamed: U4.30, X1.7
RST: C4.2, ICSP.5, R5.1, U1.29
RXI: J1.4, U1.30
SCK: ICSP.3, U1.17, X1.8
SS: U1.14, X1.6
TXO: J1.5, U1.31

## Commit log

2019-06-20 Create temp
